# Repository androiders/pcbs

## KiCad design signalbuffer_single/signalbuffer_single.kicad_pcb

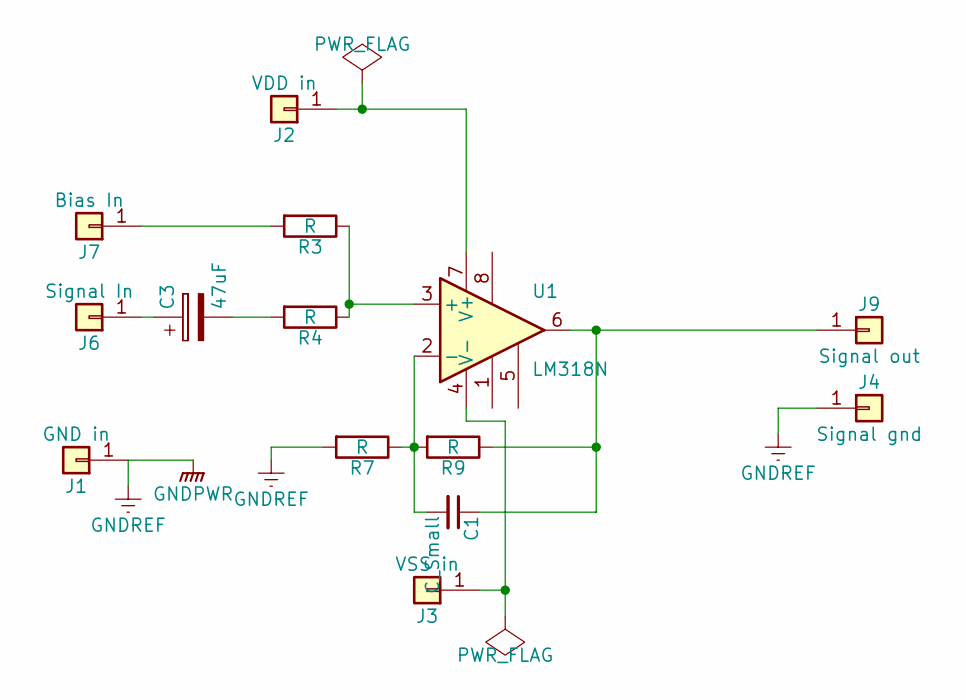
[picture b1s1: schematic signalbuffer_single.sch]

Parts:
C1: C_Small
C3: 47uF; CP_Radial_D5.0mm_P2.00mm
J1: GND in; Pin_Header_Straight_1x01_Pitch2.54mm
J2: VDD in; Pin_Header_Straight_1x01_Pitch2.54mm
J3: VSS in; Pin_Header_Straight_1x01_Pitch2.54mm
J4: Signal gnd; Pin_Header_Straight_1x01_Pitch2.54mm
J6: Signal In; Pin_Header_Straight_1x01_Pitch2.54mm
J7: Bias In; Pin_Header_Straight_1x01_Pitch2.54mm
J9: Signal out; Pin_Header_Straight_1x01_Pitch2.54mm
R3, R4, R7, R9: R; R_Axial_DIN0204_L3.6mm_D1.6mm_P5.08mm_Vertical
U1: LM318N; DIP-8_W7.62mm

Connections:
GNDPWR: J1.1, J4.1, R7.2
unnamed: C1.1, J9.1, R9.1, U1.6
unnamed: C1.2, R7.1, R9.2, U1.2 (-)
unnamed: C3.1, J6.1
unnamed: C3.2, R4.2
unnamed: J2.1, U1.7 (V+)
unnamed: J3.1, U1.4 (V-)
unnamed: J7.1, R3.2
unnamed: R3.1, R4.1, U1.3 (+)

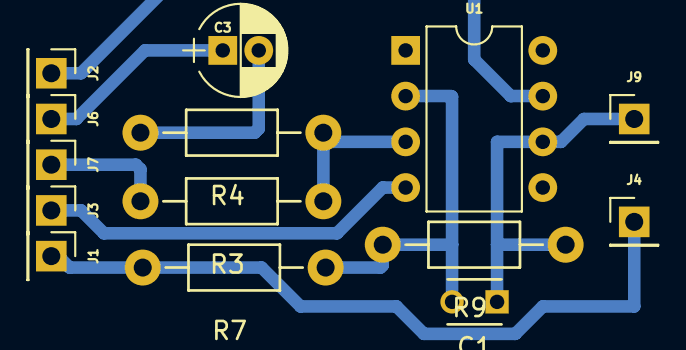
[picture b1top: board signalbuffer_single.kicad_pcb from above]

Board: 2 copper layers, 14 parts (0 on the bottom side), 9 nets.

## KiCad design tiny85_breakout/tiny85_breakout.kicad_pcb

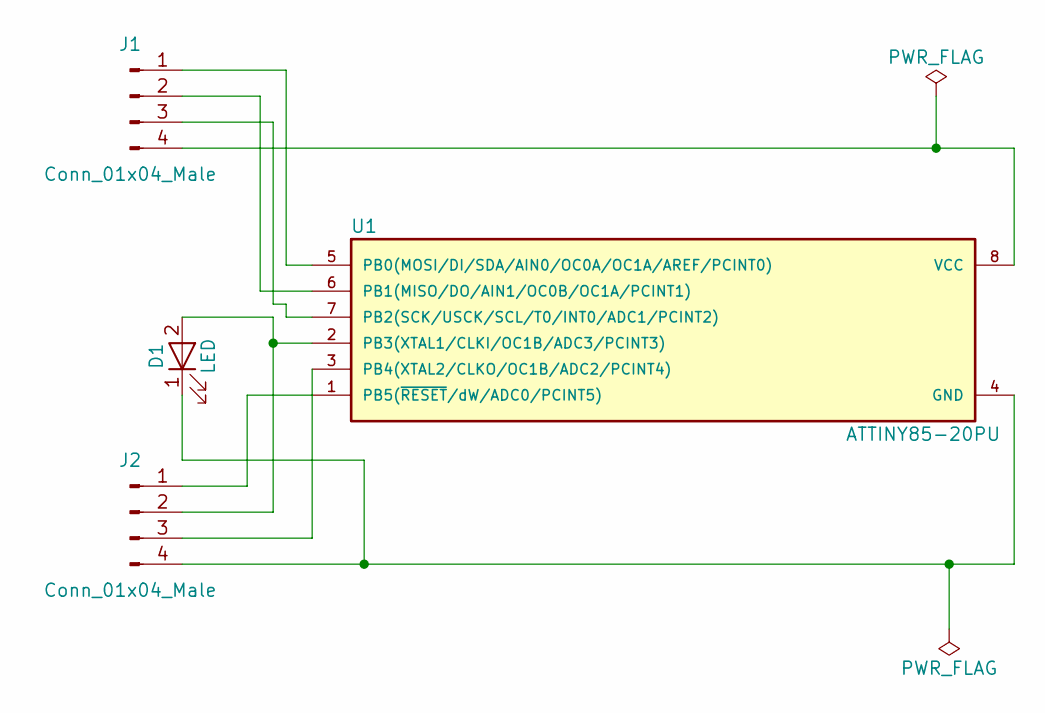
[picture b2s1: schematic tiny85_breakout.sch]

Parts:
D1: LED
J1, J2: Conn_01x04_Male
U1: ATTINY85-20PU; DIP-8_W7.62mm

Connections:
unnamed: D1.1 (K), J2.4, U1.4 (GND)
unnamed: D1.2 (A), J2.2, U1.2 (PB3(XTAL1/CLKI/OC1B/ADC3/PCINT3))
unnamed: J1.1, U1.5 (PB0(MOSI/DI/SDA/AIN0/OC0A/OC1A/AREF/PCI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)
unnamed: J1.2, U1.6 (PB1(MISO/DO/AIN1/OC0B/OC1A/PCINT1))
unnamed: J1.3, U1.7 (PB2(SCK/USCK/SCL/T0/INT0/ADC1/PCINT2))
unnamed: J1.4, U1.8 (VCC)
unnamed: J2.1, U1.1 (PB5(~RESET~/dW/ADC0/PCINT5))
unnamed: J2.3, U1.3 (PB4(XTAL2/CLKO/OC1B/ADC2/PCINT4))

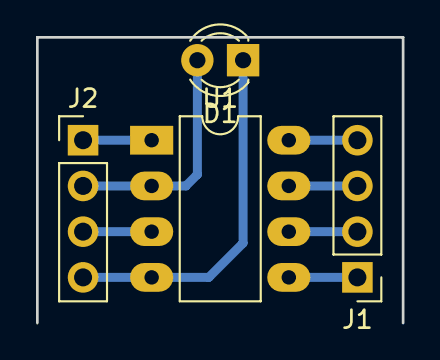
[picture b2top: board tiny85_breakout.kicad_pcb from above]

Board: 2 copper layers, 20.3 x 15.9 mm, 4 parts (0 on the bottom side), 8 nets.
